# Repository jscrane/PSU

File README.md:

View this project on [CADLAB.io](https://cadlab.io/project/1763). 

# PSU
Software-controlled variable-voltage power supply with current and power monitoring.

Features:
- Common voltages preset through web interface (In Progress)
- TFT LCD to display output voltage and current
- Digital Potentiometer for software-controlled adjustment (TODO)

## Hardware
Display hardware as [WifiWeatherGuy](https://cadlab.io/project/1280/master/files):
- [Wemos D1 Mini](https://wiki.wemos.cc/products:d1:d1_mini)
- PCB-mounted push switch
- 1.8" TFT LCD display
- v3 PCB (with pin headers)

PSU hardware:
- [LM317](https://en.wikipedia.org/wiki/LM317) variable voltage regulator
- [INA219](https://www.adafruit.com/product/904) voltage and current sensor
- [X9C103P](https://www.renesas.com/us/en/products/data-converters/digital-potentiometers/dcp/device/X9C103.html) digital potentiometer
- Old laptop transformer (19v)

## Software
- [Arduino](https://www.arduino.cc/en/main/software) 1.8.x
- [Arduino/ESP8266](https://github.com/esp8266/Arduino) 2.7.1
- [ArduinoJson](https://arduinojson.org) 6.15.1
- [TFT_eSPI](https://github.com/Bodmer/TFT_eSPI) 2.2.8
- [Adafruit_INA219](https://github.com/adafruit/Adafruit_INA219) 1.0.4
- [Arduino-X9C](https://github.com/philbowles/Arduino-X9C) 0.9.0
- [SimpleTimer](https://github.com/schinken/SimpleTimer)
- [Stator](https://github.com/PTS93/Stator)

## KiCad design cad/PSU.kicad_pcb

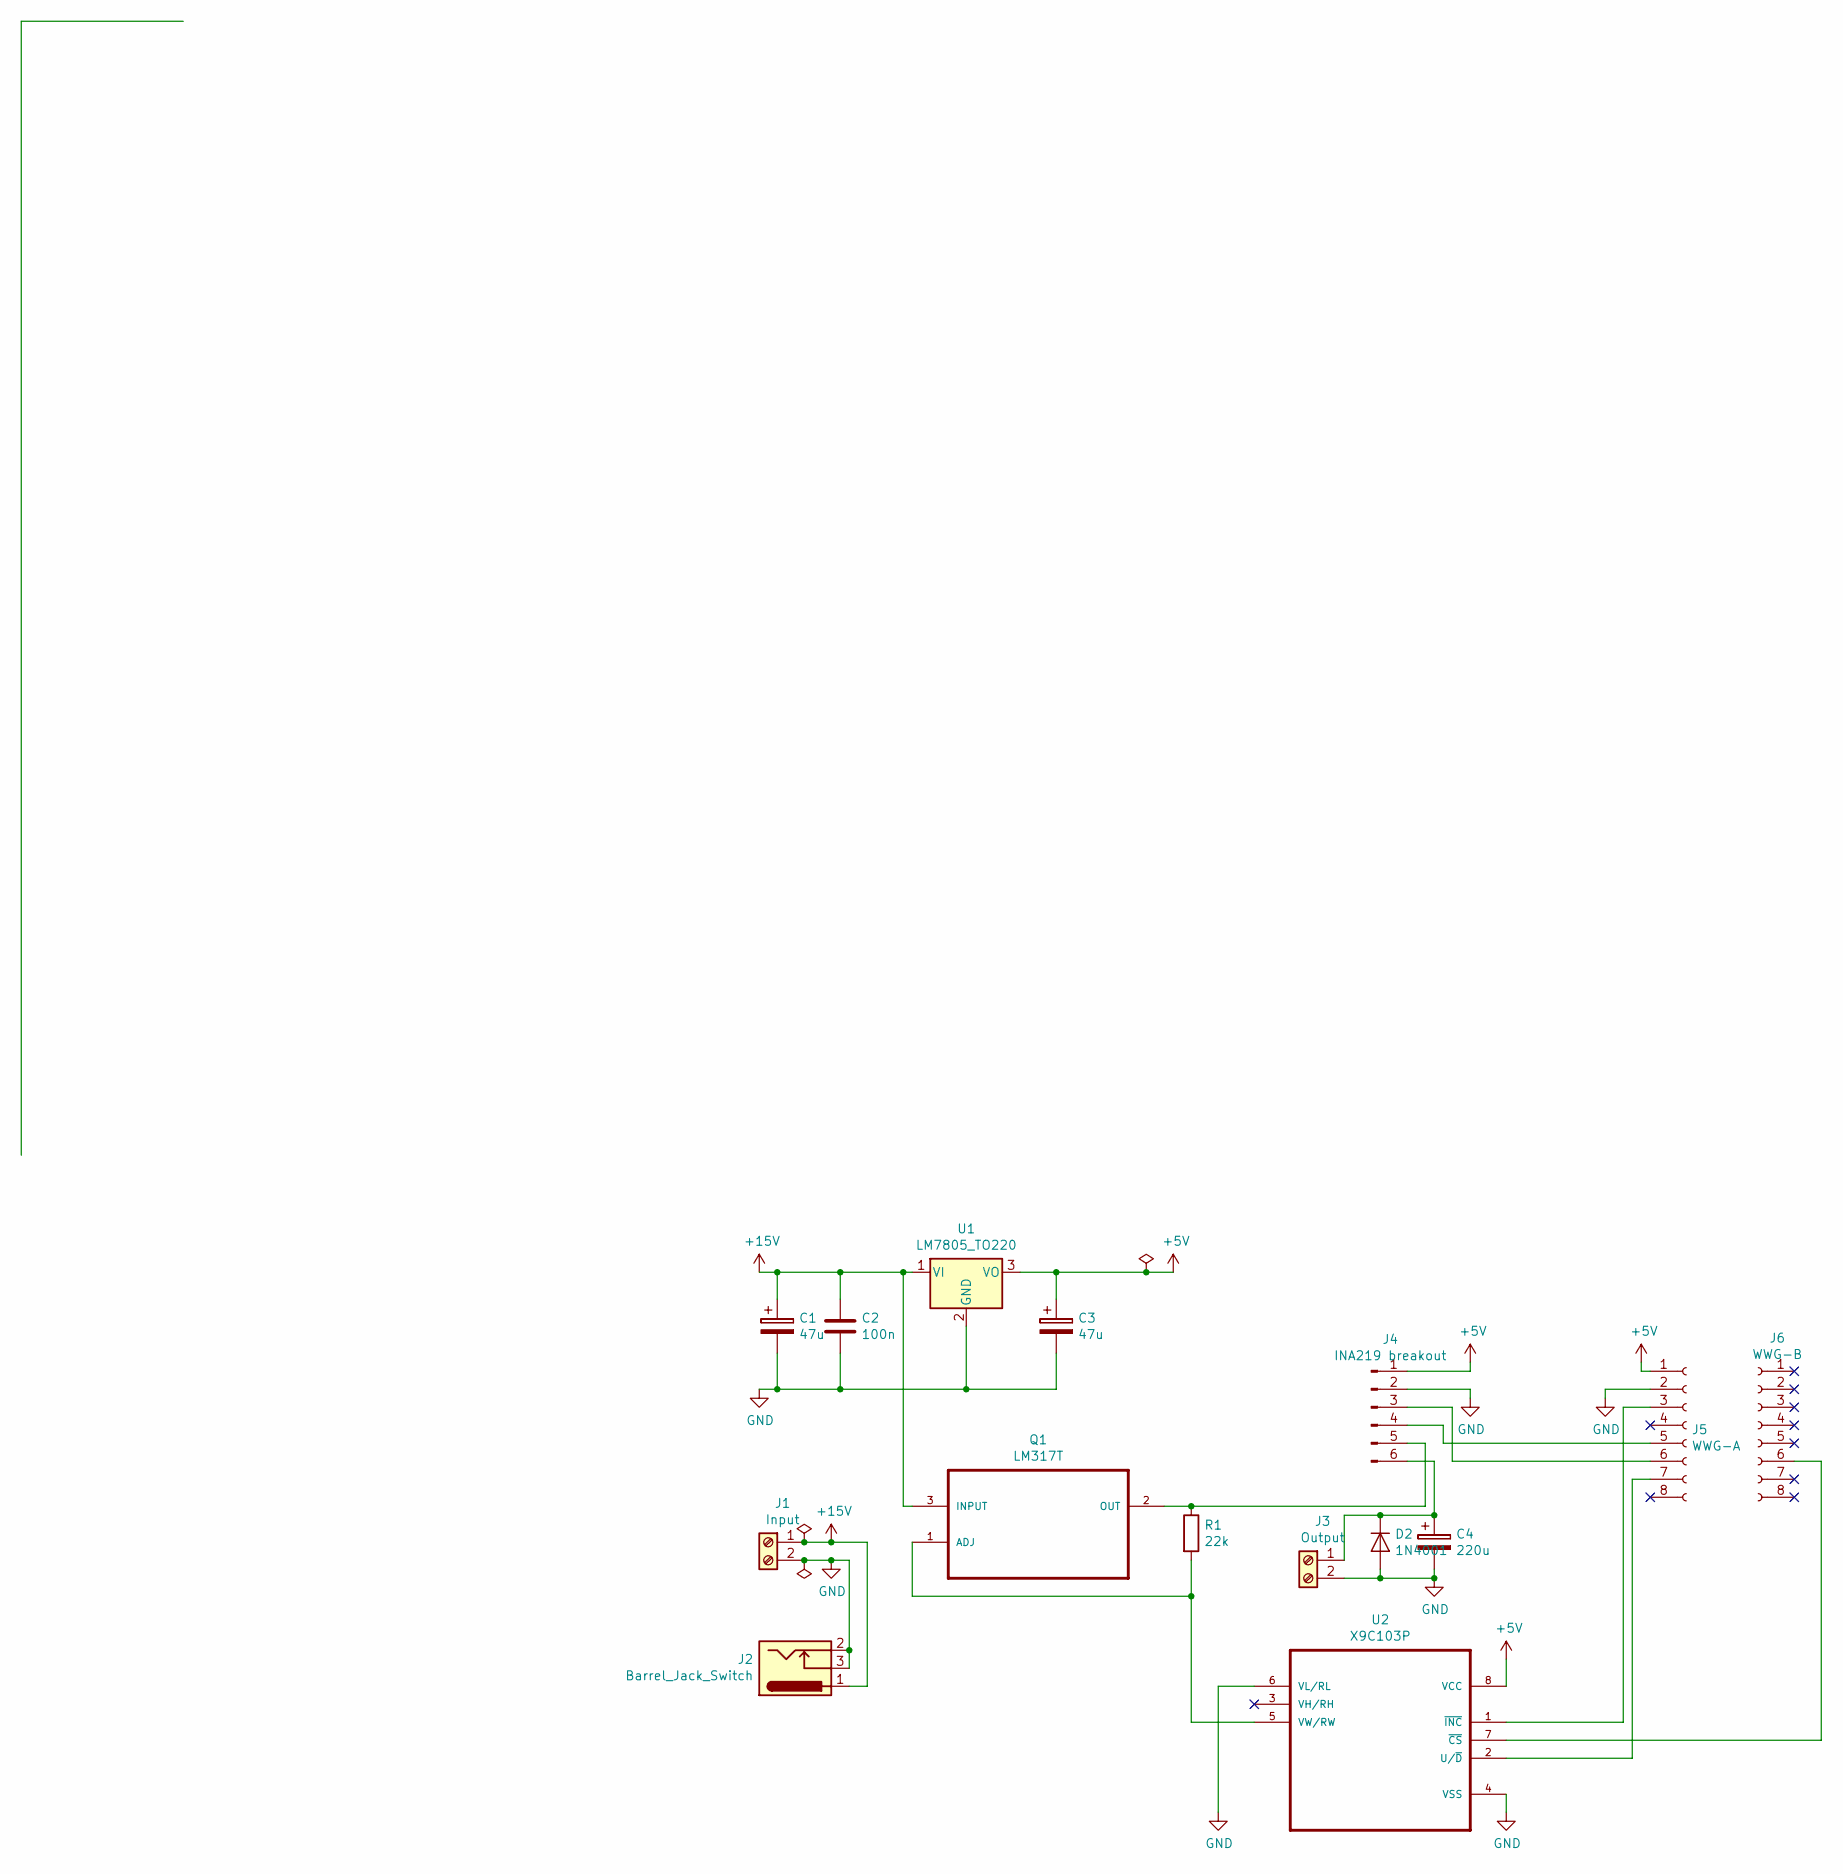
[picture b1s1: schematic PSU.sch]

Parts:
C1, C3: 47u; CP_Radial_D5.0mm_P2.00mm
C2: 100n; C_Disc_D5.0mm_W2.5mm_P5.00mm
C4: 220u; CP_Radial_D6.3mm_P2.50mm
D2: 1N4001; D_DO-41_SOD81_P10.16mm_Horizontal
J1: Input; TerminalBlock_Phoenix_PT-1,5-2-5.0-H_1x02_P5.00mm_Horizontal
J2: Barrel_Jack_Switch; BarrelJack_CUI_PJ-102AH_Horizontal
J3: Output; TerminalBlock_Phoenix_PT-1,5-2-5.0-H_1x02_P5.00mm_Horizontal
J4: INA219 breakout; PinHeader_1x06_P2.54mm_Vertical
J5: WWG-A; PinHeader_1x08_P2.54mm_Vertical
J6: WWG-B; PinHeader_1x08_P2.54mm_Vertical
Q1: LM317T; TO-220-3_Vertical
R1: 22k; R_Axial_DIN0207_L6.3mm_D2.5mm_P7.62mm_Horizontal
U1: LM7805_TO220; TO-220-3_Vertical
U2: X9C103P; DIP254P762X533-8

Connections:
+5V: C3.1, J4.1, J5.1, U1.3 (VO), U2.8 (VCC)
+15V: C1.1, C2.1, J1.1, J2.1, Q1.3 (INPUT), U1.1 (VI)
GND: C1.2, C2.2, C3.2, C4.2, D2.2 (A), J1.2, J2.2, J2.3, J3.2, J4.2, J5.2, U1.2 (GND), U2.4 (VSS), U2.6 (VL/RL)
unnamed: C4.1, D2.1 (K), J3.1, J4.6
unnamed: J4.3, J5.6
unnamed: J4.4, J5.5
unnamed: J4.5, Q1.2 (OUT), R1.1
unnamed: J5.3, U2.1 (~INC)
unnamed: J5.7, U2.2 (U/~D)
unnamed: J6.6, U2.7 (~CS)
unnamed: Q1.1 (ADJ), R1.2, U2.5 (VW/RW)

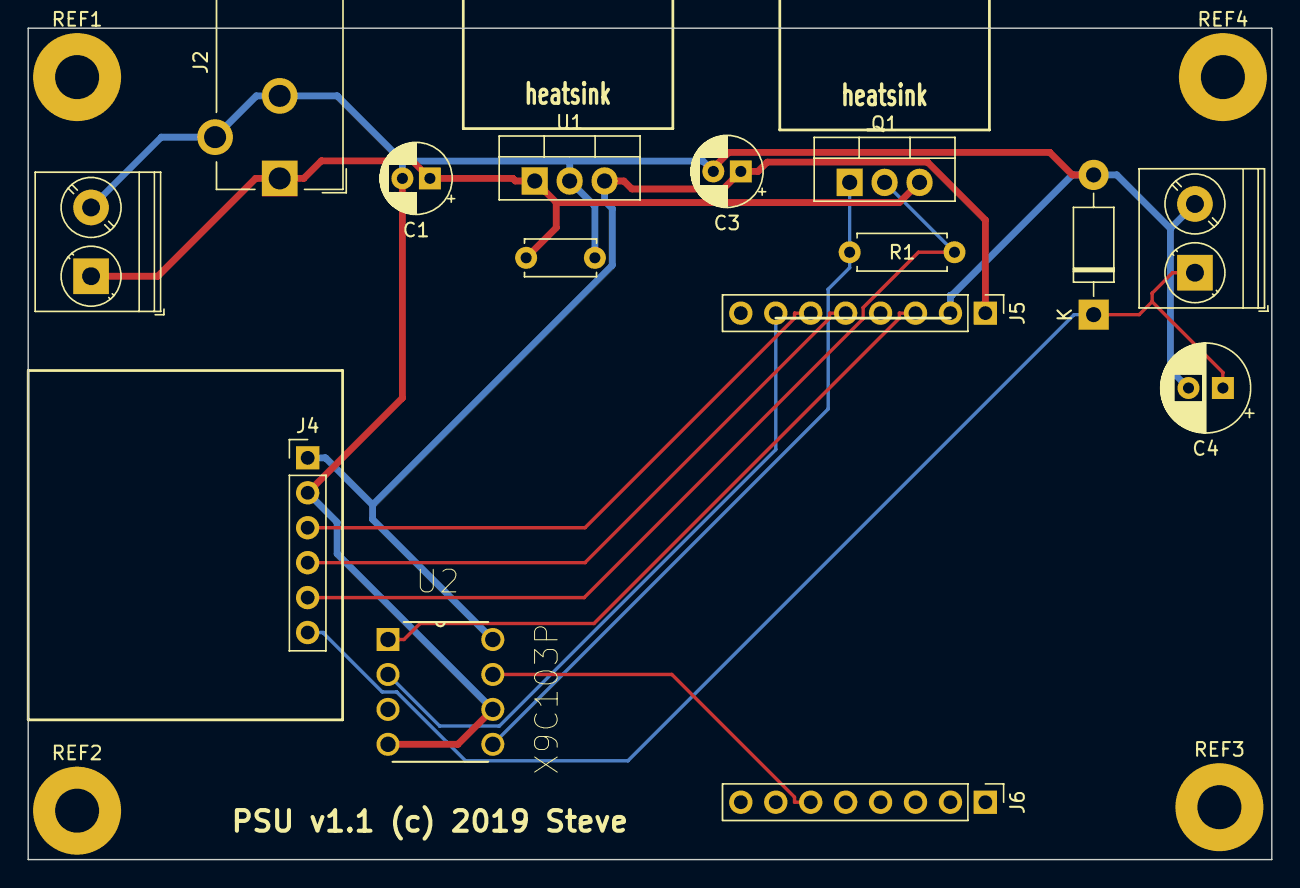
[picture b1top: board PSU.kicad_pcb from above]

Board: 2 copper layers, 90.4 x 60.5 mm, 19 parts (0 on the bottom side), 11 nets.

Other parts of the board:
REF1, REF2, REF3, REF4: MountingHole_3.2mm_M3_Pad

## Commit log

2019-01-27 Create LICENSE
2019-01-29 debug option
2019-01-29 add preset voltages
2019-01-31 use SimpleTimer lib
2019-02-02 text fonts
2019-05-10 add 12v
2019-05-10 add X9C
2019-05-10 add switch debounce
2019-05-11 add Stator lib
2019-05-11 display presets
2019-05-11 cleanup
2019-05-12 display connection status
2019-05-12 bugfix
2019-05-12 typo
2019-05-12 remove connected flag
2019-05-13 kicad
2019-05-13 Backlink to CADLAB.io has been added.
2019-05-13 add own stator class
2019-05-13 non-blocking connect
2019-05-19 add diodes, output cap
2019-05-21 renaming
2019-05-23 footprints
2019-05-23 erc check
2019-05-23 first layout
2019-05-23 change wiring to make layout easier
2019-05-23 more pcb
2019-05-26 add barrel jack and layout pcb again
2019-05-26 switch SCL and SDA again
2019-05-27 gerbers
2019-06-08 upgrade to ArduinoJson 6.x
2019-06-13 update deps
2019-06-13 bugfixes
2019-06-13 cleanup loop()
2019-06-13 version
2019-06-13 layout again
2019-06-14 text labels
2019-06-14 more cleanups
2019-06-16 sample VI at interval
2019-06-16 add smoothing
2019-06-18 v1.0 gerbers
2019-08-08 change mounting holes footprint
2019-09-12 fix #8
2020-05-22 fix #4

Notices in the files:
cad/PSU.kicad_pcb:
PSU v1.1 (c) 2019 Steve
